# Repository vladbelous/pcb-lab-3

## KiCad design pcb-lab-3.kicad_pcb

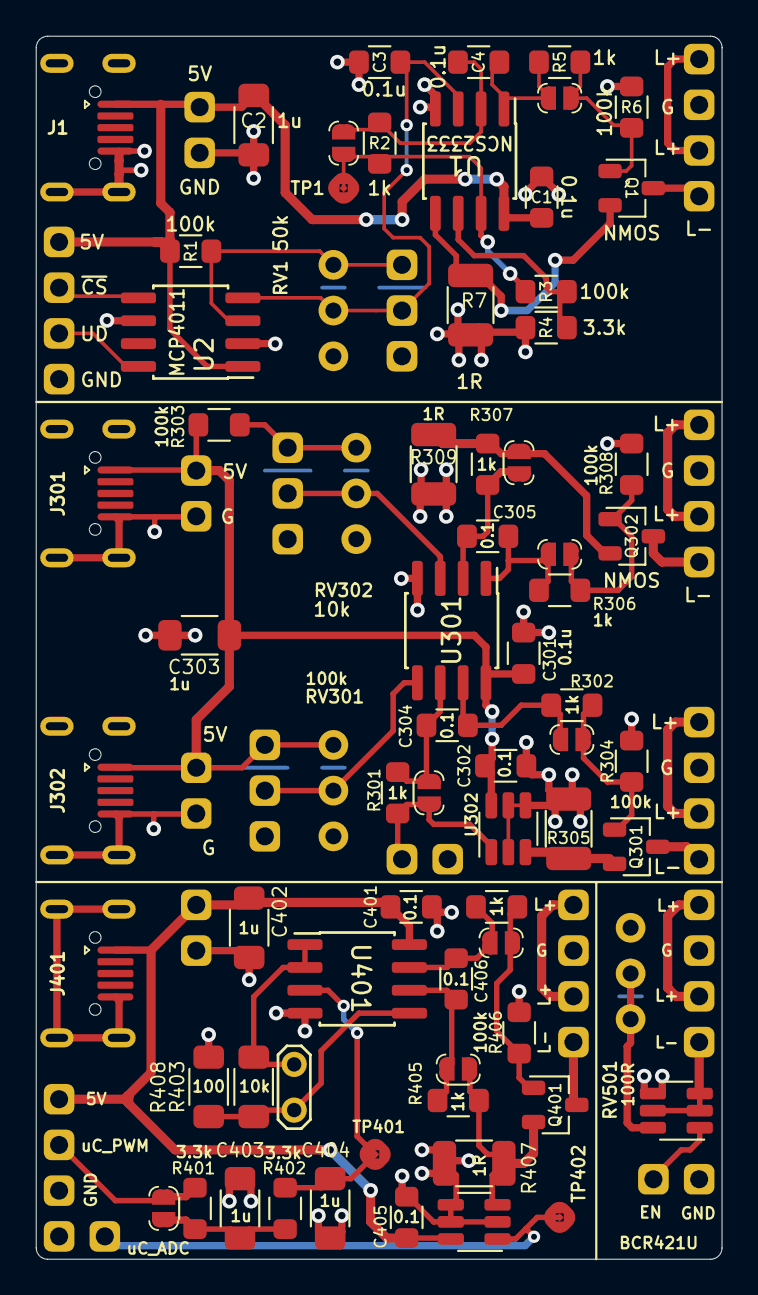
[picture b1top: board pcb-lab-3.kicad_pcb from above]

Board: 2 copper layers, 38.1 x 67.9 mm, 93 parts (0 on the bottom side), 46 nets.

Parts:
C1, C3, C4, C301, C302, C304, C305, C401, C405, C406: 0.1u; 0805_HS
C2, C303, C402, C403, C404: 1u; 1206_HS
J1, J301, J302, J401: USB_B_Micro; USB-micro-B_4-legs_Banggood
J2, J3, J4, J303, J304, J305, J306, J307, J308, J402, J403, J404, J407, J501, J502, J503: Conn_01x02; Pin_Header_Straight_1x02_Pitch2.54mm
J5, J405: Conn_01x03; Pin_Header_Straight_1x03_Pitch2.54mm
J6: Conn_01x04; Pin_Header_Straight_1x04_Pitch2.54mm
J309, J311: Conn_01x03_Female; Pin_Header_Straight_1x03_Pitch2.54mm
J310: Conn_01x02_Female; Pin_Header_Straight_1x02_Pitch2.54mm
J406: Conn_01x02_Female; TestPoint_2Pads_Pitch2.54mm_Drill0.8mm
JP1, JP2, JP301, JP302, JP303, JP304, JP401, JP402, JP403: SolderJumper_2_Open; SolderJumper-2_P1.3mm_Open
Q1, Q301, Q302, Q401: Q_NMOS_GSD; SOT-23_HS
R1, R3, R6, R303, R304, R308, R406: 100k; 0805_HS
R2, R5, R301, R302, R306, R307, R404, R405: 1k; 0805_HS
R4, R401, R402: 3.3k; 0805_HS
R7, R305, R309, R407: 1; 1210_HS
R403: 10k; 1206_HS
R408: 100; 1206_HS
RV1: 50k; RV-Pot_3-pin_2.54mm
RV301: 100k; RV-Pot_3-pin_2.54mm
RV302: 10k; RV-Pot_3-pin_2.54mm
RV501: 100; RV-Pot_3-pin_2.54mm
TP1, TP401, TP402: TestPoint; SMD-TestPoint_01x01
U1, U301, U401: NCS2333; SOIC-8_3.9x4.9mm_Pitch1.27mm_HS
U2: MCP4011; SOIC-8_3.9x4.9mm_Pitch1.27mm_HS
U302, U402: INA181; SOT-23-6_HS
U501: BCR421U; SOT-23-6_HS

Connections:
+5V: C1.1, C2.1, C301.1, C302.1, C303.1, C401.1, C402.1, C405.1, J1.1, J2.1, J6.1, J301.1, J302.1, J303.1, J304.1, J309.1, J401.1, J402.1, J405.3, R1.2, R303.2, RV301.1, U1.8, U2.1, U301.8, U302.6, U401.8, U402.6
/2-OpAmp constant current/A: J5.1, R1.1, RV1.1, U2.3
/2-OpAmp constant current/W: C3.1, J5.2, RV1.2, U1.3, U2.4
CTRL_UD: J6.3, U2.8
CTRL_~CS: J6.2, U2.5
GND: C1.2, C2.2, C3.2, C301.2, C302.2, C303.2, C401.2, C402.2, C403.1, C404.2, C405.2, J1.5, J1.6, J2.2, J3.2, J5.3, J6.4, J301.5, J301.6, J302.5, J302.6, J303.2, J304.2, J305.2, J307.2, J309.3, J310.2, J311.3, J401.5, J401.6, J402.2, J403.2, J405.1, J407.2, J501.2, J502.2, R4.1, R6.1, R7.2, R304.1, R305.2, R308.1, R309.2, R406.1, R407.2, R408.2, RV1.3, RV301.3, RV302.3, RV501.3, U1.4, U2.2, U2.6, U301.4, U302.2, U302.4, U302.5, U401.4, U402.2, U402.4, U402.5, U501.4
LOAD1+: J3.1, J4.1
LOAD1-: J4.2, Q1.3
LOAD2+: J305.1, J306.1
LOAD2-: J306.2, Q302.3
LOAD3+: J307.1, J308.1
LOAD3-: J308.2, Q301.3
LOAD4+: J403.1, J404.1
LOAD4-: J404.2, Q401.3
LOAD5+: J502.1, J503.1
LOAD5-: J503.2, U501.2, U501.3, U501.5
unnamed: C4.1, JP2.1, R5.2, U1.1
unnamed: C4.2, JP1.1, R2.2, U1.2
unnamed: C304.1, JP301.1, R301.2, U301.6
unnamed: C304.2, JP302.1, R302.2, U301.7
unnamed: C305.1, JP304.1, R307.2, U301.2
unnamed: C305.2, JP303.1, R306.2, U301.1
unnamed: C403.2, JP401.2, R401.1, R402.2
unnamed: C404.1, R402.1, TP401.1, U401.3
unnamed: C406.1, JP403.1, R405.2, U401.6
unnamed: C406.2, JP402.1, R404.2, U401.7
unnamed: J309.2, RV301.2, U301.5
unnamed: J310.1, JP301.2, R301.1, U302.1
unnamed: J311.1, R303.1, RV302.1
unnamed: J311.2, RV302.2, U301.3
unnamed: J406.1, R403.1, U401.1, U401.2
unnamed: J406.2, R403.2, R408.1, U401.5
unnamed: JP1.2, R2.1, R3.2, TP1.1, U1.7
unnamed: JP2.2, Q1.1, R5.1, R6.2
unnamed: JP302.2, Q301.1, R302.1, R304.2
unnamed: JP303.2, Q302.1, R306.1, R308.2
unnamed: JP304.2, Q302.2, R307.1, R309.1
unnamed: JP402.2, Q401.1, R404.1, R406.2
unnamed: JP403.2, Q401.2, R405.1, R407.1, U402.3
unnamed: Q1.2, R7.1, U1.5
unnamed: Q301.2, R305.1, U302.3
unnamed: R3.1, R4.2, U1.6
unnamed: RV501.1, RV501.2, U501.6
uC_ADC: J407.1, TP402.1, U402.1
uC_LED_EN: J501.1, U501.1
uC_PWM: J405.2, JP401.1, R401.2

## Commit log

2020-06-28 Initial commit. Constant current sourcing: 4 different circuits
2020-06-30 Split into hierarchical sheets. Work on 1st circuit
2020-06-30 Add connectors to all circuits
2020-07-01 Voltage divider values and current sense ranges
2020-07-02 Gate pull-down to GND instead of source
2020-07-02 Add BCR421U symbol and circuit sheet
2020-07-15 Schematic work: RC filter values
2020-07-17 Adjust usb-micro pads for easier soldering
2020-07-17 Annotate schematic and generate netlist
2020-07-17 Fix netlist to use relative project path
2020-07-17 Init PCB file and setup design rules
2020-07-17 Approx layout of 1st circuit
2020-07-17 Approx layout of all components / all circuits
2020-07-18 Tune footprints, reimport netlist
2020-07-18 Complete routing (except GND) of 1st circuit
2020-07-19 Tuned layout of 2nd circuit
2020-07-19 Complete routing (-GND) of 2nd circuit
2020-07-20 Tune layout of 3rd and 4th circuits
2020-07-20 Remove potentiometer from PWM circuit
2020-07-20 Complete routing (-GND) of 3rd an 4th circuits
2020-07-21 Ground vias
2020-07-21 Minor tuning
2020-07-21 Top and bottom silkscreen
2020-07-21 Schematic and layout pdfs

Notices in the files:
pcb-lab-3.kicad_pcb:
CC BY-SA 4.0
